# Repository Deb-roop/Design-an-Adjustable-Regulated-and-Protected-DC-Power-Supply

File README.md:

# Design-an-Adjustable-Regulated-and-Protected-DC-Power-Supply
## Adjustable, Regulated, and Protected DC Power Supply

> **Course:** ECE 2200 - Electronic Circuits Design Laboratory (Khulna University of Engineering & Technology)[cite: 1]
> **Group:** B-03[cite: 1]

### Overview and Key Features
This project features the comprehensive design, simulation, and hardware implementation of an adjustable, regulated DC power supply[cite: 1]. It efficiently converts a 230 V AC mains supply into a continuously variable DC output ranging from 1.25 V to 30 V[cite: 1]. To safeguard connected loads from electrical faults, it integrates a fast-acting MOSFET crowbar cutoff mechanism paired with operational amplifier comparators[cite: 1]. 

*   **Adjustable Output:** Utilizes the LM338K active linear voltage regulator for smooth and continuous voltage adjustments[cite: 1].
*   **Over Voltage Protection (OVP):** Automatically isolates connected loads whenever the output voltage exceeds safe operational limits[cite: 1].
*   **Under Voltage Protection (UVP):** Disconnects loads when the supply drops below a minimum threshold to prevent erratic circuit behavior[cite: 1].
*   **Short Circuit Protection (SCP):** Uses a 2N7000 MOSFET crowbar cutoff switch to rapidly suppress excessive current surges without mechanical contact bounce[cite: 1].
*   **Visual Indicators:** Integrates Red and Green status LEDs for real-time monitoring of normal power delivery and fault states[cite: 1].

---

### Core Governing Equations
The mathematical foundation of the power supply design relies on standard rectification, filtering, and active regulation principles[cite: 1]:

*   **Peak Rectified Voltage:** $V_{peak}=V_{RMS}\times\sqrt{2}-2\times V_{D}$[cite: 1]
*   **Capacitive Ripple Voltage:** $V_{ripple(p-p)}=I_{load}/(f_{ripple}\times C1)$[cite: 1]
*   **Adjustable Output Voltage:** $V_{out}=V_{ref}\times(1+RV1/R1)+I_{adj}\times RV1$[cite: 1]

---

### Experimental Performance Results
The unified system was successfully validated through Proteus ISIS software simulations and physical solderless breadboard testing over a minimum load resistance of 330 Ω[cite: 1].

| Performance Parameter | Simulation (Proteus ISIS) | Hardware Breadboard |
| :--- | :--- | :--- |
| Adjustable Voltage Range | 0.78 V - 28.2 V[cite: 1] | 1.1 V - 28.7 V[cite: 1] |
| OVP Threshold | 26.1 V[cite: 1] | 22.5 V[cite: 1] |
| UVP Threshold | 5.42 V[cite: 1] | 3.3 V[cite: 1] |
| Maximum Power Output | 1.42 W[cite: 1] | 0.94 W[cite: 1] |

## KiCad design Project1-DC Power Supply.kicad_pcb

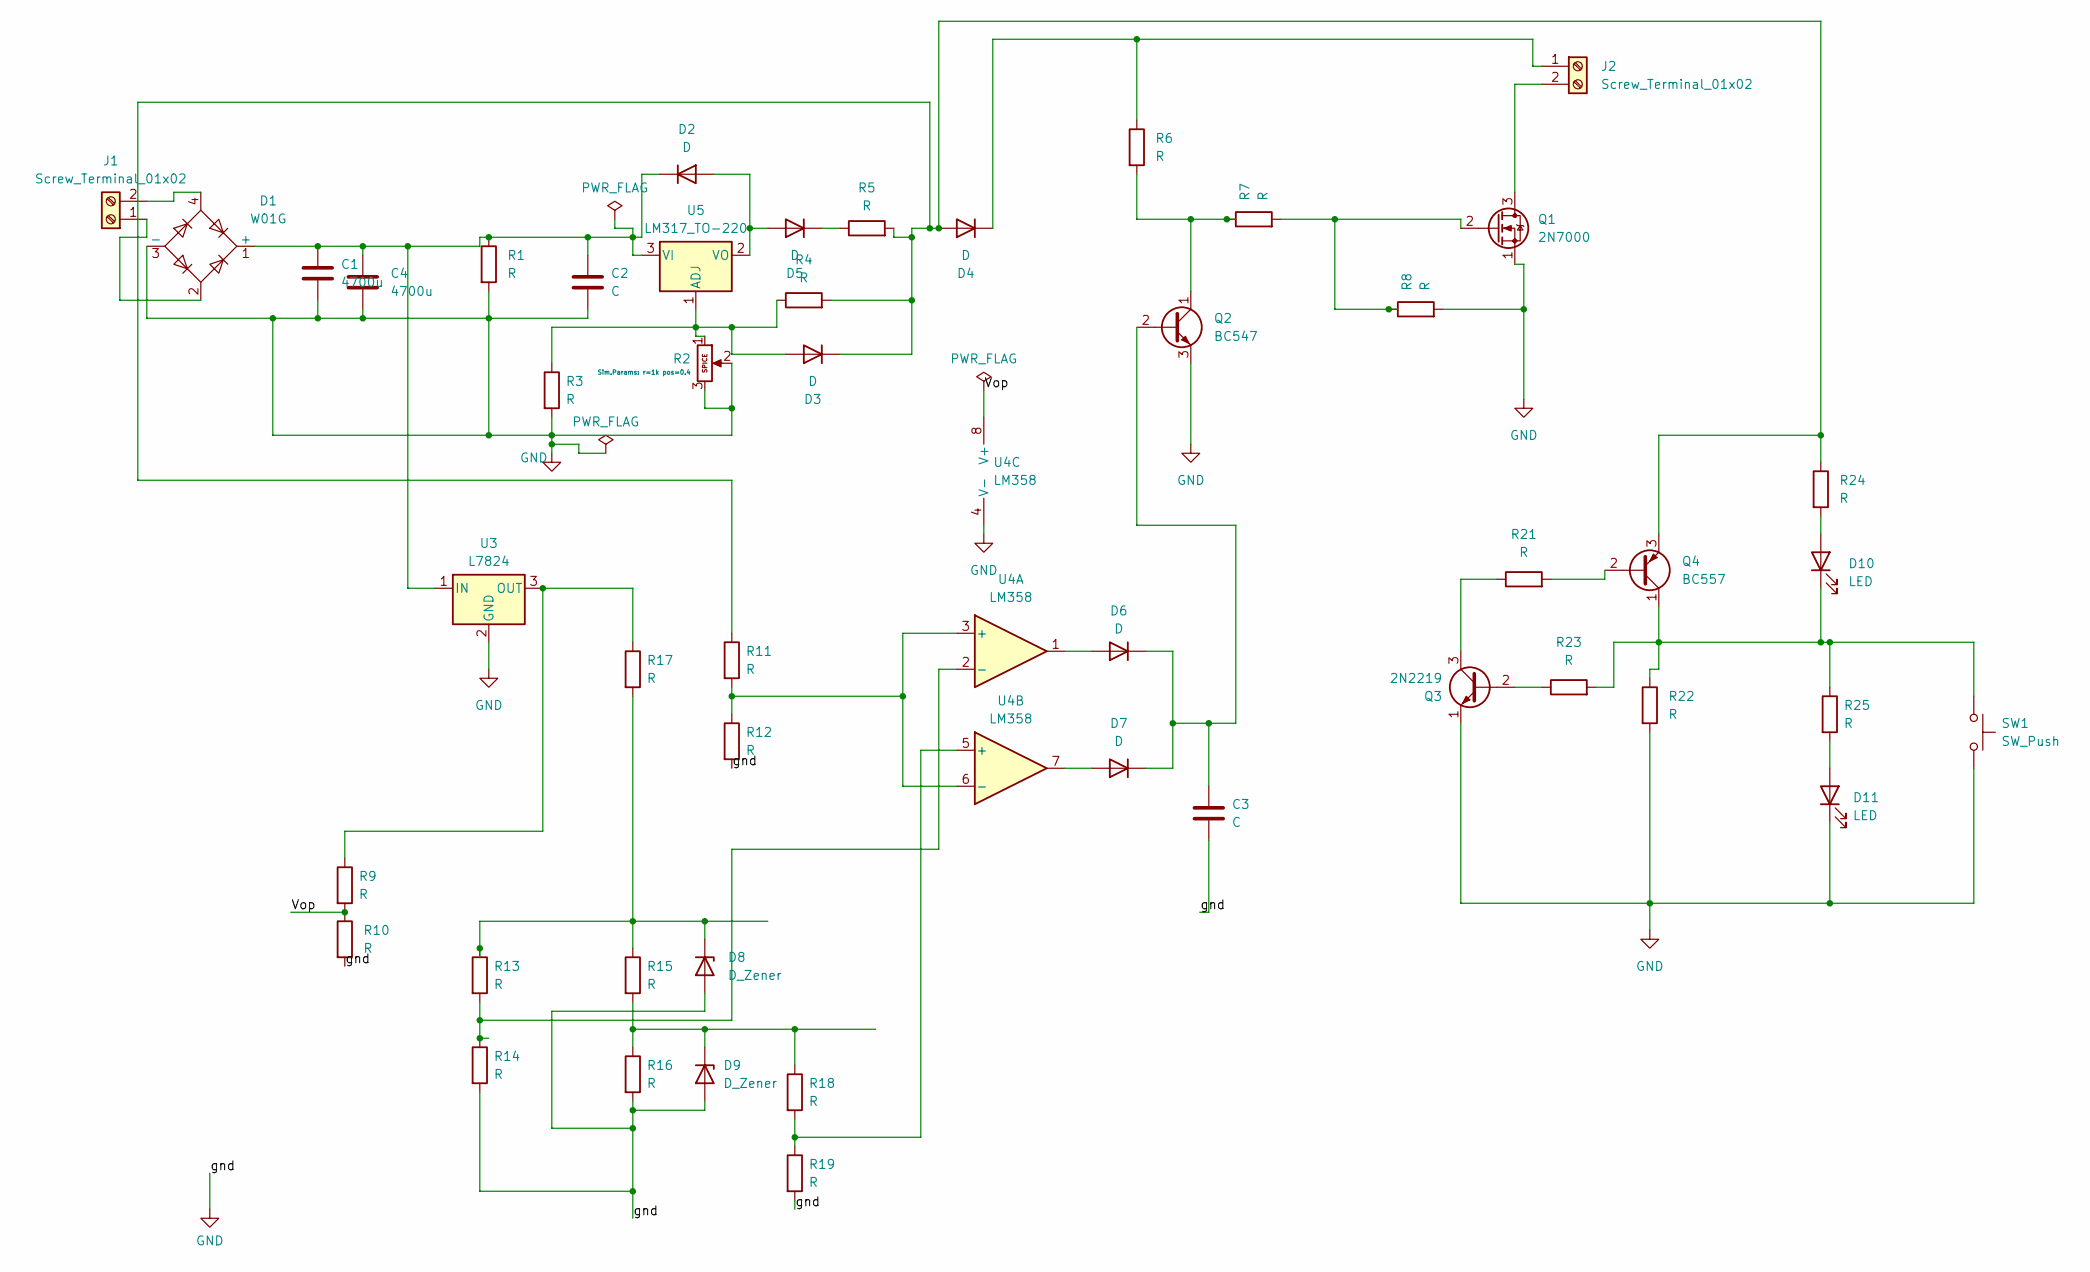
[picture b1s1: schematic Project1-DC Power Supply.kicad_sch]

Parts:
C1, C4: 4700u; C_Radial_D18.0mm_H35.5mm_P7.50mm
C2, C3: C; C_Disc_D5.0mm_W2.5mm_P5.00mm
D1: W01G; Diode_Bridge_Vishay_GBU
D2, D3, D4, D5, D6, D7: D; D_DO-41_SOD81_P10.16mm_Horizontal
D8, D9: D_Zener; D_DO-35_SOD27_P7.62mm_Horizontal
D10, D11: LED; LED_D5.0mm
J1, J2: Screw_Terminal_01x02; TerminalBlock_Phoenix_MKDS-1,5-2-5.08_1x02_P5.08mm_Horizont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
Q1: 2N7000; TO-92_Inline
Q2: BC547; TO-92_Inline
Q3: 2N2219; TO-3P-3_Vertical
Q4: BC557; TO-92_Inline
R1, R3, R4, R5, R6, R7, R8, R9, R10, R11, R12, R13, R14, R15, R16, R17, R18, R19, R21, R22, R23, R24, R25: R; R_Axial_DIN0207_L6.3mm_D2.5mm_P10.16mm_Horizontal
R2: Potentiometer; Potentiometer_Alps_RK097_Single_Horizontal
SW1: SW_Push; SW_PUSH_6mm
U3: L7824; TO-220-3_Vertical
U4: LM358; DIP-8_W7.62mm
U5: LM317_TO-220; TO-220-3_Vertical

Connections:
/Vop: R9.2, R10.1, U4.8 (V+)
GND: C1.2, C2.2, C3.2, C4.2, D1.3 (-), D8.2 (A), D9.2 (A), D11.1 (K), Q1.1 (S), Q2.3 (E), Q3.1 (E), R1.2, R2.2, R2.3, R3.2, R8.2, R10.2, R12.2, R14.2, R16.2, R19.2, R22.2, SW1.2, U3.2 (GND), U4.4 (V-)
unnamed: C1.1, C2.1, C4.1, D1.1 (+), D2.1 (K), R1.1, U3.1 (IN), U5.3 (VI)
unnamed: D2.2 (A), D5.2 (A), U5.2 (VO)
unnamed: D3.2 (A), R2.1, R3.1, R4.1, U5.1 (ADJ)
unnamed: D3.1 (K), D4.2 (A), Q4.3 (E), R4.2, R5.2, R11.1, R24.1
unnamed: D4.1 (K), J2.1, R6.1
unnamed: D5.1 (K), R5.1
unnamed: D6.2 (A), U4.1
unnamed: C3.1, D6.1 (K), D7.1 (K), Q2.2 (B)
unnamed: D7.2 (A), U4.7
unnamed: D8.1 (K), R13.1, R15.1, R17.2
unnamed: D9.1 (K), R15.2, R16.1, R18.1
unnamed: D10.2 (A), R24.2
unnamed: D10.1 (K), Q4.1 (C), R22.1, R23.2, R25.1, SW1.1
unnamed: D11.2 (A), R25.2
unnamed: D1.2, J1.1
unnamed: D1.4, J1.2
unnamed: J2.2, Q1.3 (D)
unnamed: Q1.2 (G), R7.2, R8.1
unnamed: Q2.1 (C), R6.2, R7.1
unnamed: Q3.2 (B), R23.1
unnamed: Q3.3 (C), R21.1
unnamed: Q4.2 (B), R21.2
unnamed: R9.1, R17.1, U3.3 (OUT)
unnamed: R11.2, R12.1, U4.3 (+), U4.6 (-)
unnamed: R13.2, R14.1, U4.2 (-)
unnamed: R18.2, R19.1, U4.5 (+)

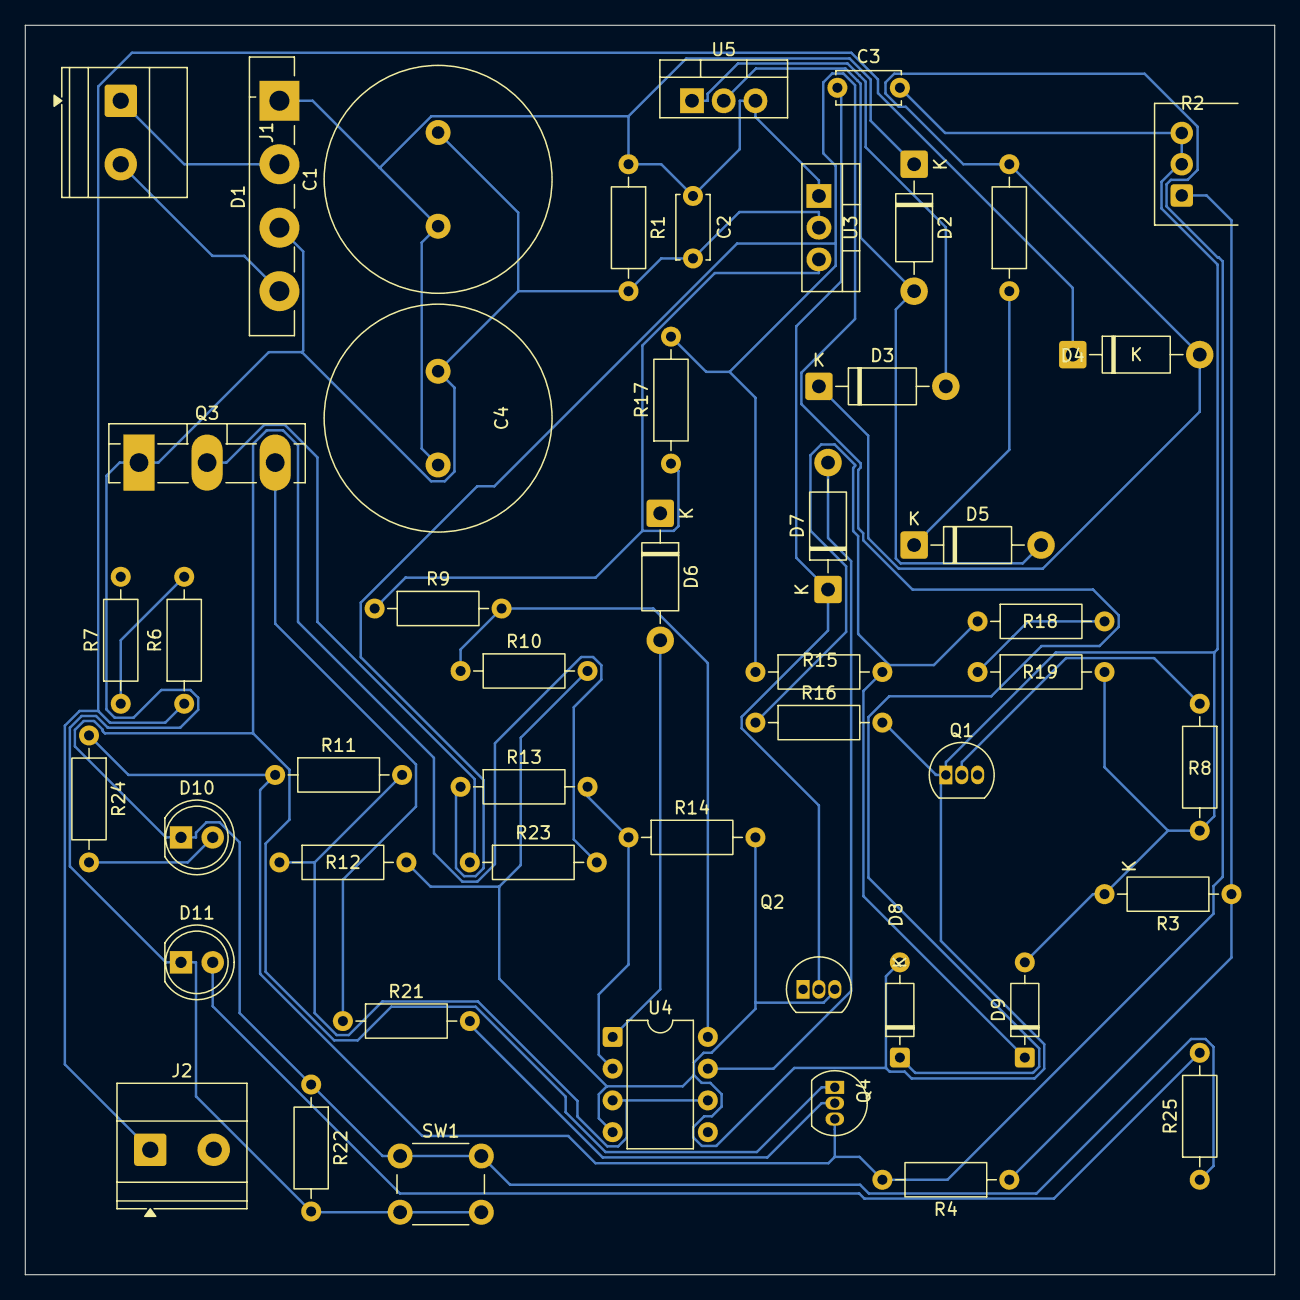
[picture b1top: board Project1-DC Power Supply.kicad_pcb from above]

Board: 2 copper layers, 100.0 x 100.0 mm, 49 parts (0 on the bottom side), 28 nets.
